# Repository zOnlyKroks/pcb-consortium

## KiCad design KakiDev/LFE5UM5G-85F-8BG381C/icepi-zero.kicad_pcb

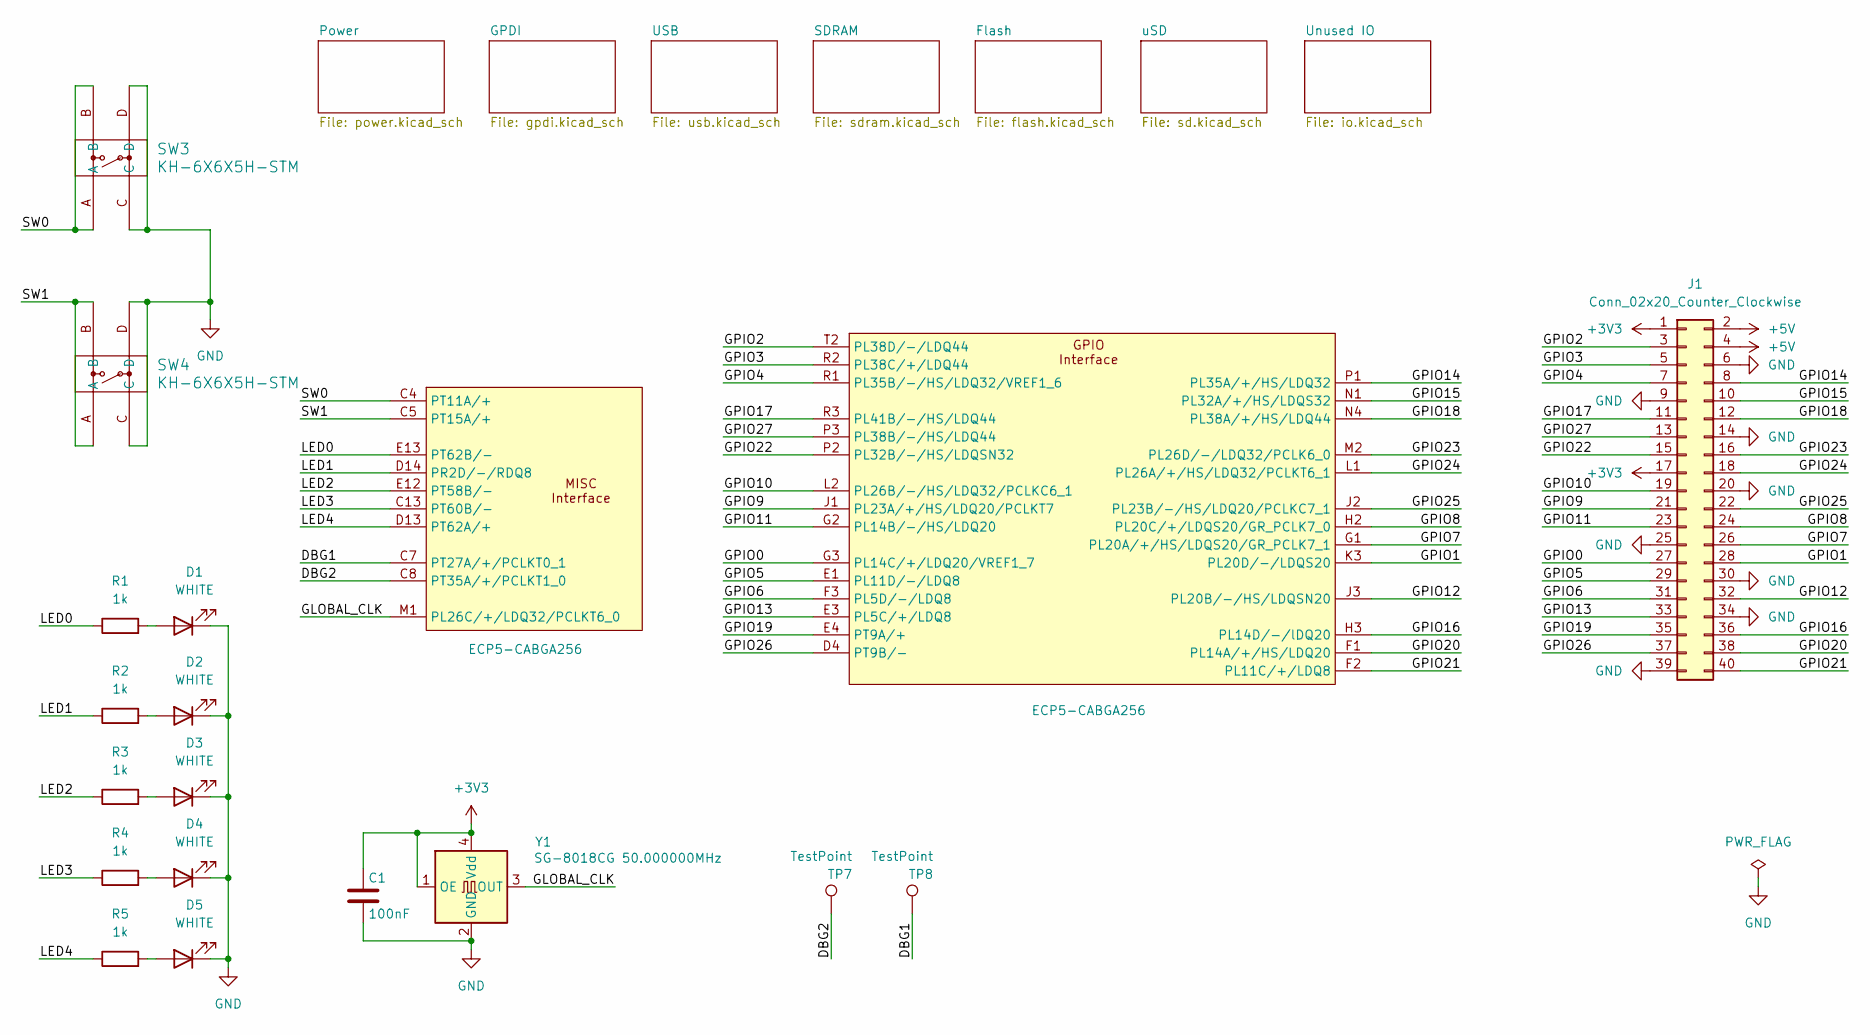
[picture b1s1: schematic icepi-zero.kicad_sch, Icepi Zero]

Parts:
C1: 100nF; C_0603_1608Metric; Manufactuer Part Number CL05B104KB54PNC; LCSC Part # C307331
D1, D2, D3, D4, D5: WHITE; LED_0603_1608Metric; Manufactuer Part Number KT-0603W; LCSC Part # C2290
J1: Conn_02x20_Counter_Clockwise; PinHeader_2x20_P2.54mm_Vertical
R1, R2, R3, R4, R5: 1k; R_0603_1608Metric; Manufactuer Part Number 0402WGF1001TCE; LCSC Part # C11702
SW3, SW4: KH-6X6X5H-STM; KH-6X6X5H-STM_SKE
TP7, TP8: TestPoint; TestPoint_Pad_D1.0mm
U1: ECP5-CABGA256; BGA-256_14.0x14.0mm_Layout16x16_P0.8mm_Ball0.45mm_Pad0.32mm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; Manufactuer Part Number LFE5U-25F-6BG256C; LCSC Part # C1521614
Y1: SG-8018CG 50.000000MHz; Oscillator_SMD_SiT_PQFN-4Pin_2.5x2.0mm; Manufactuer Part Number SG-8018CG 50.000000MHz TJHSA; LCSC Part # C390526

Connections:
+3V3: C1.1, J1.1, J1.17, Y1.1 (OE), Y1.4 (Vdd); also elsewhere on the board
+5V: J1.2, J1.4; also elsewhere on the board
/DBG1: TP8.1 (1_1), U1.C7 (PT27A/+/PCLKT0_1)
/DBG2: TP7.1 (1_1), U1.C8 (PT35A/+/PCLKT1_0)
/GLOBAL_CLK: U1.M1 (PL26C/+/LDQ32/PCLKT6_0), Y1.3 (OUT)
/GPIO0: J1.27, U1.G3 (PL14C/+/LDQ20/VREF1_7)
/GPIO1: J1.28, U1.K3 (PL20D/-/LDQS20)
/GPIO2: J1.3, U1.T2 (PL38D/-/LDQ44)
/GPIO3: J1.5, U1.R2 (PL38C/+/LDQ44)
/GPIO4: J1.7, U1.R1 (PL35B/-/HS/LDQ32/VREF1_6)
/GPIO5: J1.29, U1.E1 (PL11D/-/LDQ8)
/GPIO6: J1.31, U1.F3 (PL5D/-/LDQ8)
/GPIO7: J1.26, U1.G1 (PL20A/+/HS/LDQS20/GR_PCLK7_1)
/GPIO8: J1.24, U1.H2 (PL20C/+/LDQS20/GR_PCLK7_0)
/GPIO9: J1.21, U1.J1 (PL23A/+/HS/LDQ20/PCLKT7)
/GPIO10: J1.19, U1.L2 (PL26B/-/HS/LDQ32/PCLKC6_1)
/GPIO11: J1.23, U1.G2 (PL14B/-/HS/LDQ20)
/GPIO12: J1.32, U1.J3 (PL20B/-/HS/LDQSN20)
/GPIO13: J1.33, U1.E3 (PL5C/+/LDQ8)
/GPIO14: J1.8, U1.P1 (PL35A/+/HS/LDQ32)
/GPIO15: J1.10, U1.N1 (PL32A/+/HS/LDQS32)
/GPIO16: J1.36, U1.H3 (PL14D/-/lDQ20)
/GPIO17: J1.11, U1.R3 (PL41B/-/HS/LDQ44)
/GPIO18: J1.12, U1.N4 (PL38A/+/HS/LDQ44)
/GPIO19: J1.35, U1.E4 (PT9A/+)
/GPIO20: J1.38, U1.F1 (PL14A/+/HS/LDQ20)
/GPIO21: J1.40, U1.F2 (PL11C/+/LDQ8)
/GPIO22: J1.15, U1.P2 (PL32B/-/HS/LDQSN32)
/GPIO23: J1.16, U1.M2 (PL26D/-/LDQ32/PCLK6_0)
/GPIO24: J1.18, U1.L1 (PL26A/+/HS/LDQ32/PCLKT6_1)
/GPIO25: J1.22, U1.J2 (PL23B/-/HS/LDQ20/PCLKC7_1)
/GPIO26: J1.37, U1.D4 (PT9B/-)
/GPIO27: J1.13, U1.P3 (PL38B/-/HS/LDQ44)
/LED0: R1.1, U1.E13 (PT62B/-)
/LED1: R2.1, U1.D14 (PR2D/-/RDQ8)
/LED2: R3.1, U1.E12 (PT58B/-)
/LED3: R4.1, U1.C13 (PT60B/-)
/LED4: R5.1, U1.D13 (PT62A/+)
/SW0: SW3.A, SW3.B, U1.C4 (PT11A/+)
/SW1: SW4.A, SW4.B, U1.C5 (PT15A/+)
GND: C1.2, D1.1 (K), D2.1 (K), D3.1 (K), D4.1 (K), D5.1 (K), J1.6, J1.9, J1.14, J1.20, J1.25, J1.30, J1.34, J1.39, SW3.C, SW3.D, SW4.C, SW4.D, Y1.2 (GND); also elsewhere on the board
unnamed: D1.2 (A), R1.2
unnamed: D2.2 (A), R2.2
unnamed: D3.2 (A), R3.2
unnamed: D4.2 (A), R4.2
unnamed: D5.2 (A), R5.2

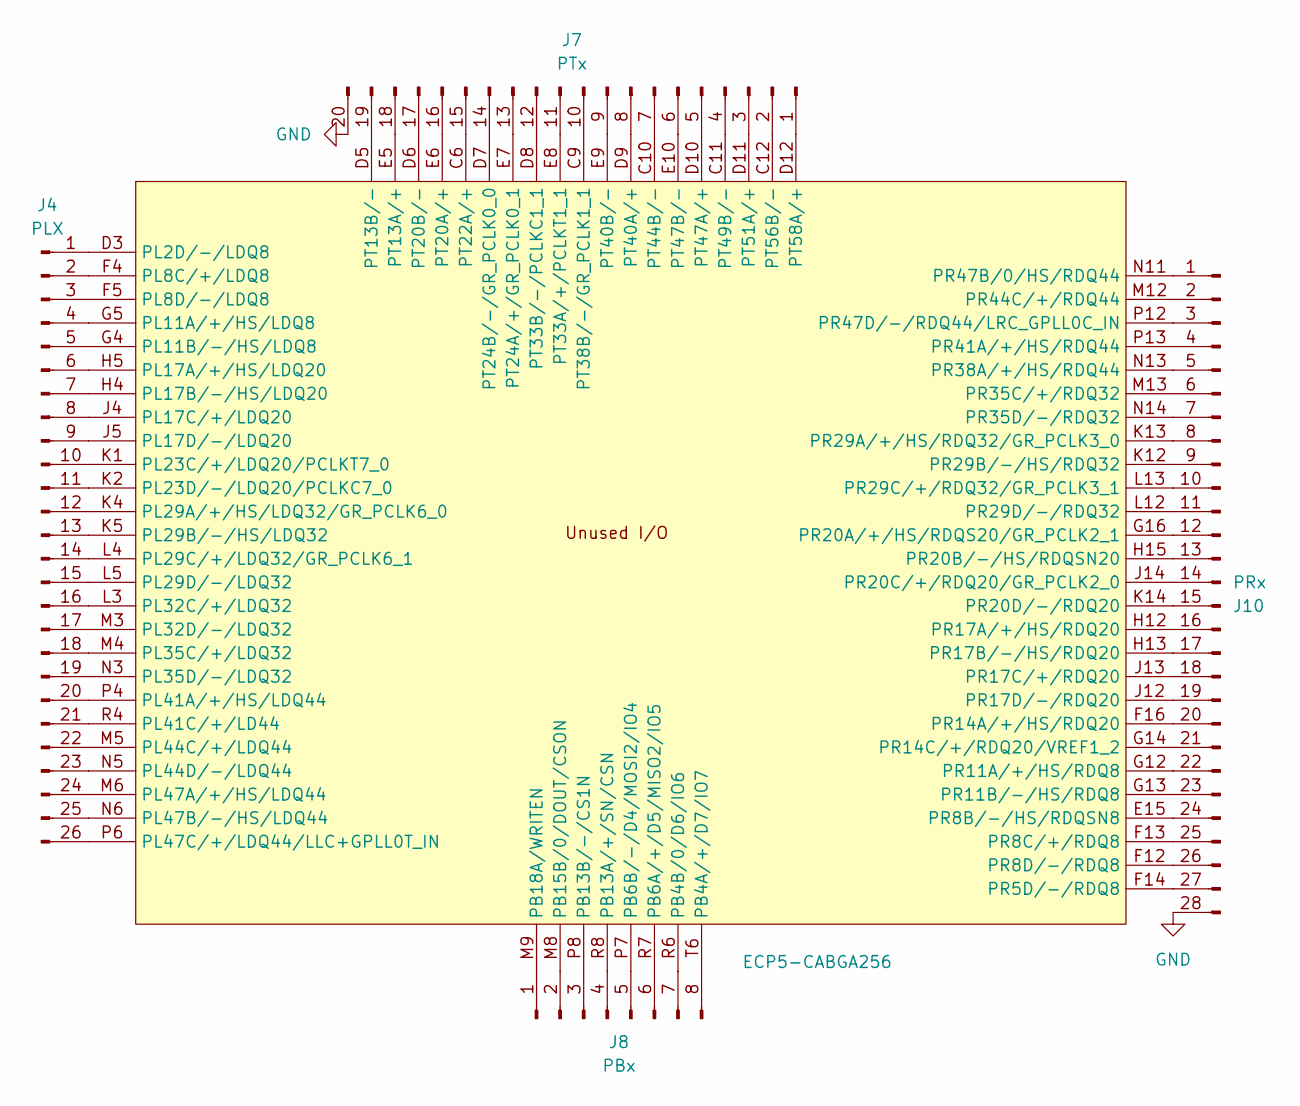
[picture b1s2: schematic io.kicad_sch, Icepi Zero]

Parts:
J4: PLX; PinHeader_2x13_P2.54mm_Vertical
J7: PTx; PinHeader_2x10_P2.54mm_Vertical
J8: PBx; PinHeader_2x04_P2.54mm_Vertical
J10: PRx; PinHeader_2x14_P2.54mm_Vertical
U1: ECP5-CABGA256; BGA-256_14.0x14.0mm_Layout16x16_P0.8mm_Ball0.45mm_Pad0.32mm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; Manufactuer Part Number LFE5U-25F-6BG256C; LCSC Part # C1521614

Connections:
GND: J7.20, J10.28; also elsewhere on the board
unnamed: J4.1, U1.D3 (PL2D/-/LDQ8)
unnamed: J4.2, U1.F4 (PL8C/+/LDQ8)
unnamed: J4.3, U1.F5 (PL8D/-/LDQ8)
unnamed: J4.4, U1.G5 (PL11A/+/HS/LDQ8)
unnamed: J4.5, U1.G4 (PL11B/-/HS/LDQ8)
unnamed: J4.6, U1.H5 (PL17A/+/HS/LDQ20)
unnamed: J4.7, U1.H4 (PL17B/-/HS/LDQ20)
unnamed: J4.8, U1.J4 (PL17C/+/LDQ20)
unnamed: J4.9, U1.J5 (PL17D/-/LDQ20)
unnamed: J4.10, U1.K1 (PL23C/+/LDQ20/PCLKT7_0)
unnamed: J4.11, U1.K2 (PL23D/-/LDQ20/PCLKC7_0)
unnamed: J4.12, U1.K4 (PL29A/+/HS/LDQ32/GR_PCLK6_0)
unnamed: J4.13, U1.K5 (PL29B/-/HS/LDQ32)
unnamed: J4.14, U1.L4 (PL29C/+/LDQ32/GR_PCLK6_1)
unnamed: J4.15, U1.L5 (PL29D/-/LDQ32)
unnamed: J4.16, U1.L3 (PL32C/+/LDQ32)
unnamed: J4.17, U1.M3 (PL32D/-/LDQ32)
unnamed: J4.18, U1.M4 (PL35C/+/LDQ32)
unnamed: J4.19, U1.N3 (PL35D/-/LDQ32)
unnamed: J4.20, U1.P4 (PL41A/+/HS/LDQ44)
unnamed: J4.21, U1.R4 (PL41C/+/LD44)
unnamed: J4.22, U1.M5 (PL44C/+/LDQ44)
unnamed: J4.23, U1.N5 (PL44D/-/LDQ44)
unnamed: J4.24, U1.M6 (PL47A/+/HS/LDQ44)
unnamed: J4.25, U1.N6 (PL47B/-/HS/LDQ44)
unnamed: J4.26, U1.P6 (PL47C/+/LDQ44/LLC+GPLL0T_IN)
unnamed: J7.1, U1.D12 (PT58A/+)
unnamed: J7.2, U1.C12 (PT56B/-)
unnamed: J7.3, U1.D11 (PT51A/+)
unnamed: J7.4, U1.C11 (PT49B/-)
unnamed: J7.5, U1.D10 (PT47A/+)
unnamed: J7.6, U1.E10 (PT47B/-)
unnamed: J7.7, U1.C10 (PT44B/-)
unnamed: J7.8, U1.D9 (PT40A/+)
unnamed: J7.9, U1.E9 (PT40B/-)
unnamed: J7.10, U1.C9 (PT38B/-/GR_PCLK1_1)
unnamed: J7.11, U1.E8 (PT33A/+/PCLKT1_1)
unnamed: J7.12, U1.D8 (PT33B/-/PCLKC1_1)
unnamed: J7.13, U1.E7 (PT24A/+/GR_PCLK0_1)
unnamed: J7.14, U1.D7 (PT24B/-/GR_PCLK0_0)
unnamed: J7.15, U1.C6 (PT22A/+)
unnamed: J7.16, U1.E6 (PT20A/+)
unnamed: J7.17, U1.D6 (PT20B/-)
unnamed: J7.18, U1.E5 (PT13A/+)
unnamed: J7.19, U1.D5 (PT13B/-)
unnamed: J8.1, U1.M9 (PB18A/WRITEN)
unnamed: J8.2, U1.M8 (PB15B/0/DOUT/CSON)
unnamed: J8.3, U1.P8 (PB13B/-/CS1N)
unnamed: J8.4, U1.R8 (PB13A/+/SN/CSN)
unnamed: J8.5, U1.P7 (PB6B/-/D4/MOSI2/IO4)
unnamed: J8.6, U1.R7 (PB6A/+/D5/MISO2/IO5)
unnamed: J8.7, U1.R6 (PB4B/0/D6/IO6)
unnamed: J8.8, U1.T6 (PB4A/+/D7/IO7)
unnamed: J10.1, U1.N11 (PR47B/0/HS/RDQ44)
unnamed: J10.2, U1.M12 (PR44C/+/RDQ44)
unnamed: J10.3, U1.P12 (PR47D/-/RDQ44/LRC_GPLL0C_IN)
unnamed: J10.4, U1.P13 (PR41A/+/HS/RDQ44)
unnamed: J10.5, U1.N13 (PR38A/+/HS/RDQ44)
unnamed: J10.6, U1.M13 (PR35C/+/RDQ32)
unnamed: J10.7, U1.N14 (PR35D/-/RDQ32)
unnamed: J10.8, U1.K13 (PR29A/+/HS/RDQ32/GR_PCLK3_0)
unnamed: J10.9, U1.K12 (PR29B/-/HS/RDQ32)
unnamed: J10.10, U1.L13 (PR29C/+/RDQ32/GR_PCLK3_1)
unnamed: J10.11, U1.L12 (PR29D/-/RDQ32)
unnamed: J10.12, U1.G16 (PR20A/+/HS/RDQS20/GR_PCLK2_1)
unnamed: J10.13, U1.H15 (PR20B/-/HS/RDQSN20)
unnamed: J10.14, U1.J14 (PR20C/+/RDQ20/GR_PCLK2_0)
unnamed: J10.15, U1.K14 (PR20D/-/RDQ20)
unnamed: J10.16, U1.H12 (PR17A/+/HS/RDQ20)
unnamed: J10.17, U1.H13 (PR17B/-/HS/RDQ20)
unnamed: J10.18, U1.J13 (PR17C/+/RDQ20)
unnamed: J10.19, U1.J12 (PR17D/-/RDQ20)
unnamed: J10.20, U1.F16 (PR14A/+/HS/RDQ20)
unnamed: J10.21, U1.G14 (PR14C/+/RDQ20/VREF1_2)
unnamed: J10.22, U1.G12 (PR11A/+/HS/RDQ8)
unnamed: J10.23, U1.G13 (PR11B/-/HS/RDQ8)
unnamed: J10.24, U1.E15 (PR8B/-/HS/RDQSN8)
unnamed: J10.25, U1.F13 (PR8C/+/RDQ8)
unnamed: J10.26, U1.F12 (PR8D/-/RDQ8)
unnamed: J10.27, U1.F14 (PR5D/-/RDQ8)

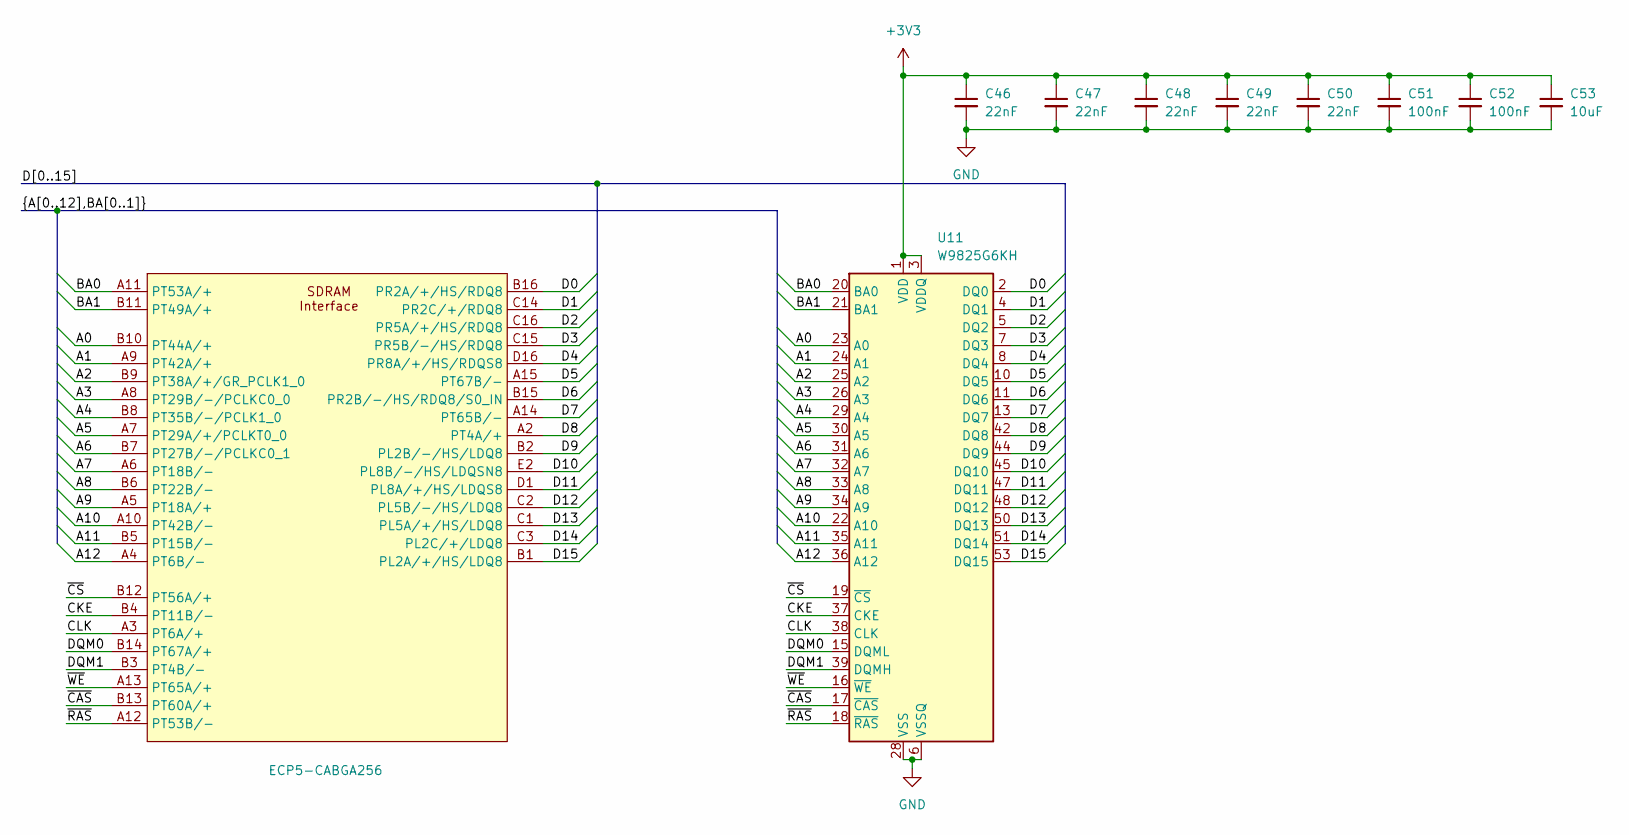
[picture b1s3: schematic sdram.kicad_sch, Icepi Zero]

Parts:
C46, C47, C48, C49, C50: 22nF; C_0603_1608Metric; Manufactuer Part Number 0603B223K500NT; LCSC Part # C77571
C51, C52: 100nF; C_0603_1608Metric; Manufactuer Part Number 0603B223K500NT; LCSC Part # C77571
C53: 10uF; C_0603_1608Metric; Manufactuer Part Number CL10A106KP8NNNC; LCSC Part # C19702
U1: ECP5-CABGA256; BGA-256_14.0x14.0mm_Layout16x16_P0.8mm_Ball0.45mm_Pad0.32mm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; Manufactuer Part Number LFE5U-25F-6BG256C; LCSC Part # C1521614
U11: W9825G6KH; TSOP-II-54_22.2x10.16mm_P0.8mm; Manufactuer Part Number W9825G6KH-6; LCSC Part # C62246

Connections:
+3V3: C46.1, C47.1, C48.1, C49.1, C50.1, C51.1, C52.1, C53.1, U11.1 (VDD), U11.3 (VDDQ), U11.9 (VDDQ), U11.14 (VDD), U11.27 (VDD), U11.43 (VDDQ), U11.49 (VDDQ); also elsewhere on the board
/SDRAM/A0: U1.B10 (PT44A/+), U11.23 (A0)
/SDRAM/A1: U1.A9 (PT42A/+), U11.24 (A1)
/SDRAM/A2: U1.B9 (PT38A/+/GR_PCLK1_0), U11.25 (A2)
/SDRAM/A3: U1.A8 (PT29B/-/PCLKC0_0), U11.26 (A3)
/SDRAM/A4: U1.B8 (PT35B/-/PCLK1_0), U11.29 (A4)
/SDRAM/A5: U1.A7 (PT29A/+/PCLKT0_0), U11.30 (A5)
/SDRAM/A6: U1.B7 (PT27B/-/PCLKC0_1), U11.31 (A6)
/SDRAM/A7: U1.A6 (PT18B/-), U11.32 (A7)
/SDRAM/A8: U1.B6 (PT22B/-), U11.33 (A8)
/SDRAM/A9: U1.A5 (PT18A/+), U11.34 (A9)
/SDRAM/A10: U1.A10 (PT42B/-), U11.22 (A10)
/SDRAM/A11: U1.B5 (PT15B/-), U11.35 (A11)
/SDRAM/A12: U1.A4 (PT6B/-), U11.36 (A12)
/SDRAM/BA0: U1.A11 (PT53A/+), U11.20 (BA0)
/SDRAM/BA1: U1.B11 (PT49A/+), U11.21 (BA1)
/SDRAM/CKE: U1.B4 (PT11B/-), U11.37 (CKE)
/SDRAM/CLK: U1.A3 (PT6A/+), U11.38 (CLK)
/SDRAM/D0: U1.B16 (PR2A/+/HS/RDQ8), U11.2 (DQ0)
/SDRAM/D1: U1.C14 (PR2C/+/RDQ8), U11.4 (DQ1)
/SDRAM/D2: U1.C16 (PR5A/+/HS/RDQ8), U11.5 (DQ2)
/SDRAM/D3: U1.C15 (PR5B/-/HS/RDQ8), U11.7 (DQ3)
/SDRAM/D4: U1.D16 (PR8A/+/HS/RDQS8), U11.8 (DQ4)
/SDRAM/D5: U1.A15 (PT67B/-), U11.10 (DQ5)
/SDRAM/D6: U1.B15 (PR2B/-/HS/RDQ8/S0_IN), U11.11 (DQ6)
/SDRAM/D7: U1.A14 (PT65B/-), U11.13 (DQ7)
/SDRAM/D8: U1.A2 (PT4A/+), U11.42 (DQ8)
/SDRAM/D9: U1.B2 (PL2B/-/HS/LDQ8), U11.44 (DQ9)
/SDRAM/D10: U1.E2 (PL8B/-/HS/LDQSN8), U11.45 (DQ10)
/SDRAM/D11: U1.D1 (PL8A/+/HS/LDQS8), U11.47 (DQ11)
/SDRAM/D12: U1.C2 (PL5B/-/HS/LDQ8), U11.48 (DQ12)
/SDRAM/D13: U1.C1 (PL5A/+/HS/LDQ8), U11.50 (DQ13)
/SDRAM/D14: U1.C3 (PL2C/+/LDQ8), U11.51 (DQ14)
/SDRAM/D15: U1.B1 (PL2A/+/HS/LDQ8), U11.53 (DQ15)
/SDRAM/DQM0: U1.B14 (PT67A/+), U11.15 (DQML)
/SDRAM/DQM1: U1.B3 (PT4B/-), U11.39 (DQMH)
/SDRAM/~CAS: U1.B13 (PT60A/+), U11.17 (~CAS)
/SDRAM/~CS: U1.B12 (PT56A/+), U11.19 (~CS)
/SDRAM/~RAS: U1.A12 (PT53B/-), U11.18 (~RAS)
/SDRAM/~WE: U1.A13 (PT65A/+), U11.16 (~WE)
GND: C46.2, C47.2, C48.2, C49.2, C50.2, C51.2, C52.2, C53.2, U11.6 (VSSQ), U11.12 (VSSQ), U11.28 (VSS), U11.41 (VSS), U11.46 (VSSQ), U11.52 (VSSQ), U11.54 (VSS); also elsewhere on the board

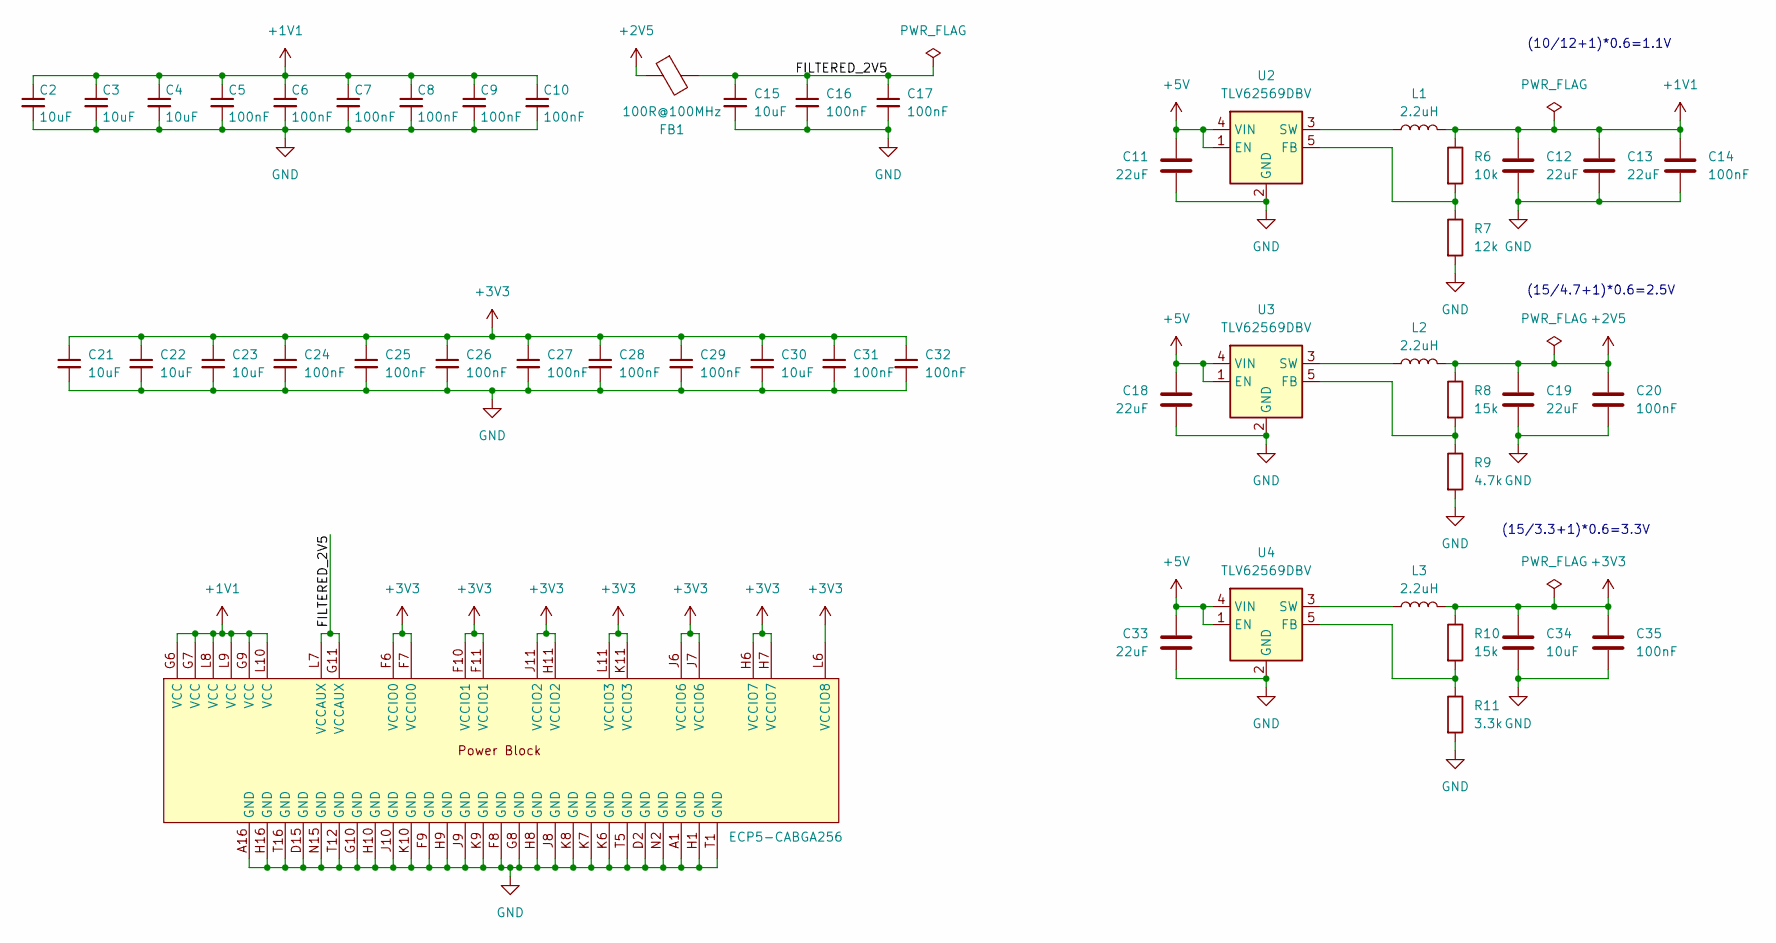
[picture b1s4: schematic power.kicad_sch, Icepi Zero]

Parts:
C2, C3, C4, C15, C21, C22, C23, C30, C34: 10uF; C_0603_1608Metric; Manufactuer Part Number CL10A106KP8NNNC; LCSC Part # C19702
C5, C6, C7, C8, C9, C10, C14, C16, C17, C20, C24, C25, C26, C27, C28, C29, C31, C32, C35: 100nF; C_0603_1608Metric; Manufactuer Part Number CL05B104KB54PNC; LCSC Part # C307331
C11, C12, C13, C18, C19, C33: 22uF; C_0603_1608Metric; Manufactuer Part Number CL10A226MQ8NRNC; LCSC Part # C59461
FB1: 100R@100MHz; L_0805_2012Metric; Manufactuer Part Number CBG201209U101T; LCSC Part # C74480
L1, L2, L3: 2.2uH; L_0805_2012Metric; Manufactuer Part Number TDK MLP2012S2R2MT0S1; LCSC Part # C107322
R6: 10k; R_0603_1608Metric; Manufactuer Part Number 0402WGF1002TCE; LCSC Part # C25744
R7: 12k; R_0603_1608Metric; Manufactuer Part Number 0402WGF1202TCE; LCSC Part # C25752
R8, R10: 15k; R_0603_1608Metric; Manufactuer Part Number 0402WGF1502TCE; LCSC Part # C25756
R9: 4.7k; R_0603_1608Metric; Manufactuer Part Number 0402WGF4701TCE; LCSC Part # C25900
R11: 3.3k; R_0603_1608Metric; Manufactuer Part Number 0402WGF3301TCE; LCSC Part # C25890
U1: ECP5-CABGA256; BGA-256_14.0x14.0mm_Layout16x16_P0.8mm_Ball0.45mm_Pad0.32mm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; Manufactuer Part Number LFE5U-25F-6BG256C; LCSC Part # C1521614
U2, U3, U4: TLV62569DBV; SOT-23-5; Manufactuer Part Number TLV62569DBVR; LCSC Part # C141836

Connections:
+1V1: C2.1, C3.1, C4.1, C5.1, C6.1, C7.1, C8.1, C9.1, C10.1, C12.1, C13.1, C14.1, L1.2, R6.1, U1.G6 (VCC), U1.G7 (VCC), U1.G9 (VCC), U1.L8 (VCC), U1.L9 (VCC), U1.L10 (VCC)
+2V5: C19.1, C20.1, FB1.1, L2.2, R8.1
+3V3: C21.1, C22.1, C23.1, C24.1, C25.1, C26.1, C27.1, C28.1, C29.1, C30.1, C31.1, C32.1, C34.1, C35.1, L3.2, R10.1, U1.F6 (VCCIO0), U1.F7 (VCCIO0), U1.F10 (VCCIO1), U1.F11 (VCCIO1), U1.H6 (VCCIO7), U1.H7 (VCCIO7), U1.H11 (VCCIO2), U1.J6 (VCCIO6), U1.J7 (VCCIO6), U1.J11 (VCCIO2), U1.K11 (VCCIO3), U1.L6 (VCCIO8), U1.L11 (VCCIO3); also elsewhere on the board
+5V: C11.1, C18.1, C33.1, U2.1 (EN), U2.4 (VIN), U3.1 (EN), U3.4 (VIN), U4.1 (EN), U4.4 (VIN); also elsewhere on the board
/Power/FILTERED_2V5: C15.1, C16.1, C17.1, FB1.2, U1.G11 (VCCAUX), U1.L7 (VCCAUX)
GND: C2.2, C3.2, C4.2, C5.2, C6.2, C7.2, C8.2, C9.2, C10.2, C11.2, C12.2, C13.2, C14.2, C15.2, C16.2, C17.2, C18.2, C19.2, C20.2, C21.2, C22.2, C23.2, C24.2, C25.2, C26.2, C27.2, C28.2, C29.2, C30.2, C31.2, C32.2, C33.2, C34.2, C35.2, R7.2, R9.2, R11.2, U1.A1 (GND), U1.A16 (GND), U1.D2 (GND), U1.D15 (GND), U1.F8 (GND), U1.F9 (GND), U1.G8 (GND), U1.G10 (GND), U1.H1 (GND), U1.H8 (GND), U1.H9 (GND), U1.H10 (GND), U1.H16 (GND), U1.J8 (GND), U1.J9 (GND), U1.J10 (GND), U1.K6 (GND), U1.K7 (GND), U1.K8 (GND), U1.K9 (GND), U1.K10 (GND), U1.N2 (GND), U1.N15 (GND), U1.T1 (GND), U1.T5 (GND), U1.T12 (GND), U1.T16 (GND), U2.2 (GND), U3.2 (GND), U4.2 (GND); also elsewhere on the board
unnamed: R6.2, R7.1, U2.5 (FB)
unnamed: L1.1, U2.3 (SW)
unnamed: R8.2, R9.1, U3.5 (FB)
unnamed: L2.1, U3.3 (SW)
unnamed: R10.2, R11.1, U4.5 (FB)
unnamed: L3.1, U4.3 (SW)

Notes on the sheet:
(15/4.7+1)*0.6=2.5V
(10/12+1)*0.6=1.1V
(15/3.3+1)*0.6=3.3V

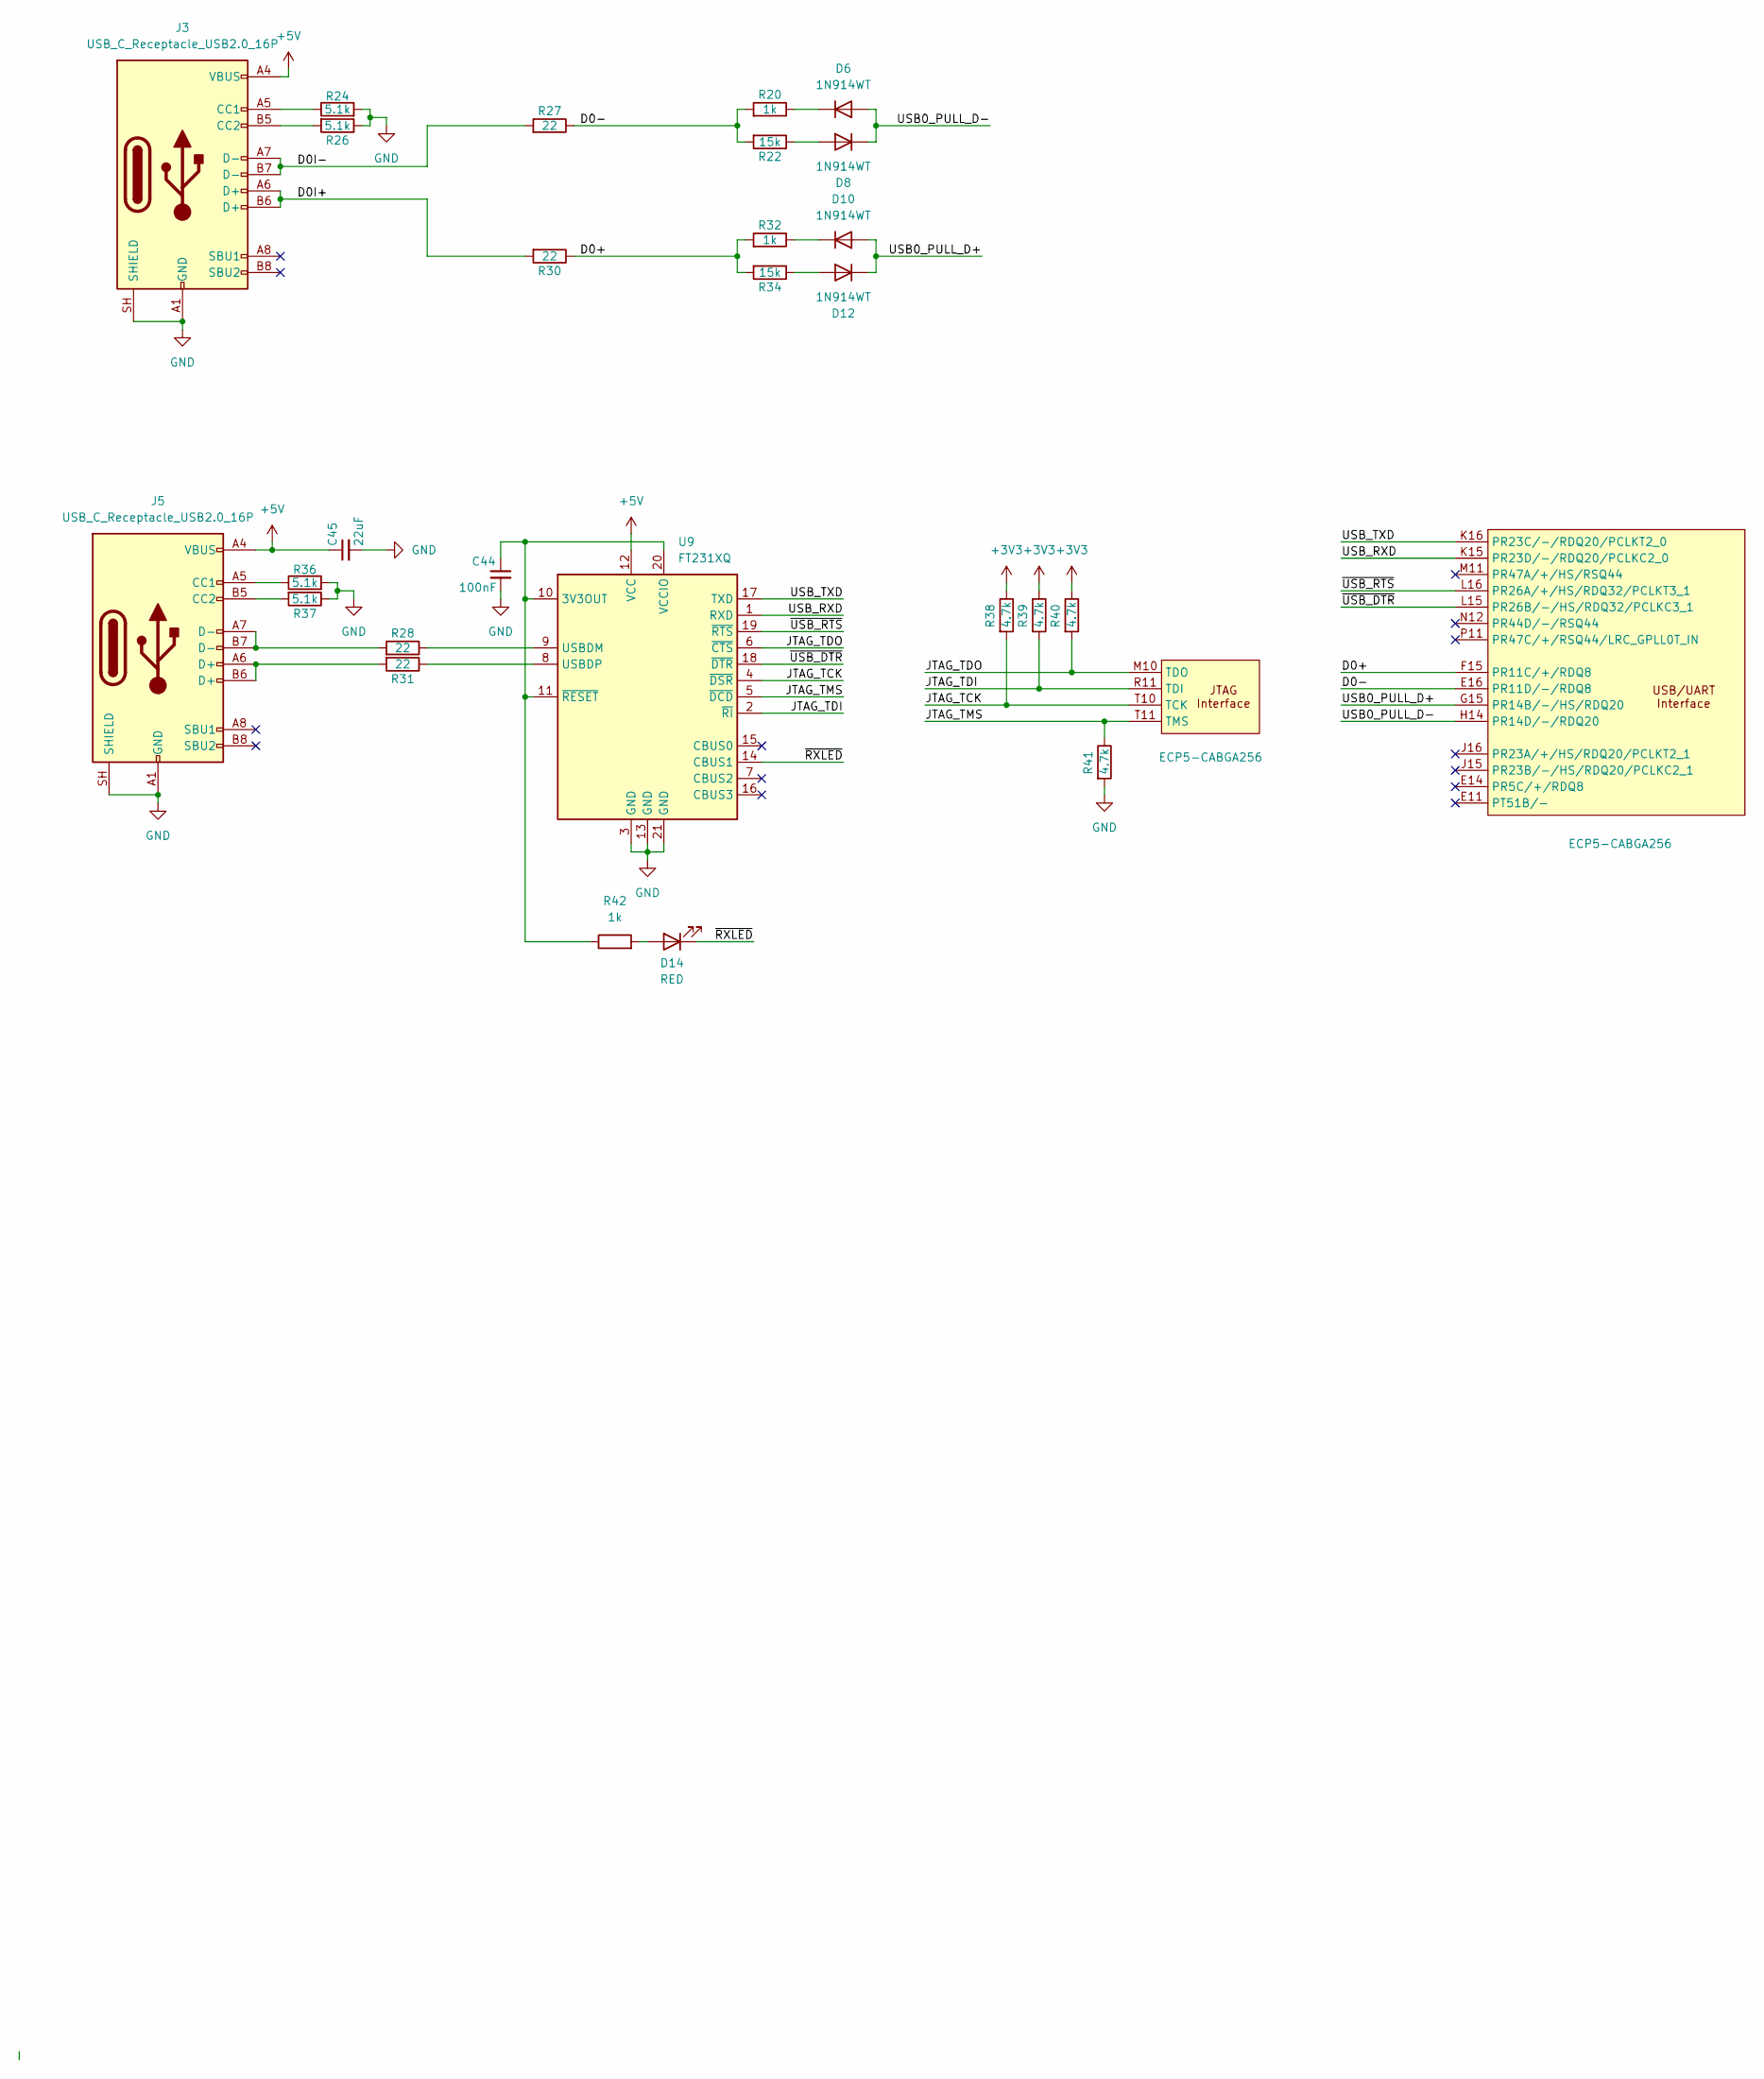
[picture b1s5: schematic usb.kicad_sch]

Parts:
C44: 100nF; C_0603_1608Metric; Manufactuer Part Number CL05B104KB54PNC; LCSC Part # C307331
C45: 22uF; C_0603_1608Metric; Manufactuer Part Number CL10A226MQ8NRNC; LCSC Part # C59461
D6, D8, D10, D12: 1N914WT; D_SOD-523; Manufactuer Part Number 1N914WT; LCSC Part # C2836064
D14: RED; LED_0603_1608Metric; Manufactuer Part Number KT-0603R; LCSC Part # C2286
J3, J5: USB_C_Receptacle_USB2.0_16P; USB_C_Receptacle_HRO_TYPE-C-31-M-12
R20, R32, R42: 1k; R_0603_1608Metric; Manufactuer Part Number 0402WGF1001TCE; LCSC Part # C11702
R22: 15k; R_0603_1608Metric; Manufactuer Part Number 0402WGF1502TCE; LCSC Part # C25756
R24, R26, R36, R37: 5.1k; R_0603_1608Metric; Manufactuer Part Number 0402WGF5101TCE; LCSC Part # C25905
R27, R28, R30, R31: 22; R_0603_1608Metric; Manufactuer Part Number 0201WMF270JTEE; LCSC Part # C473051
R34: 15k; R_0402_1005Metric; Manufactuer Part Number 0402WGF1502TCE; LCSC Part # C25756
R38, R39, R40, R41: 4.7k; R_0603_1608Metric; Manufactuer Part Number 0402WGF4701TCE; LCSC Part # C25900
U1: ECP5-CABGA256; BGA-256_14.0x14.0mm_Layout16x16_P0.8mm_Ball0.45mm_Pad0.32mm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; Manufactuer Part Number LFE5U-25F-6BG256C; LCSC Part # C1521614
U9: FT231XQ; QFN-20-1EP_4x4mm_P0.5mm_EP2.5x2.5mm; Manufactuer Part Number FT231XQ-R; LCSC Part # C132159

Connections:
+3V3: R38.1, R39.1, R40.1; also elsewhere on the board
+5V: C45.1, J3.A4 (VBUS), J3.A9 (VBUS), J3.B4 (VBUS), J3.B9 (VBUS), J5.A4 (VBUS), J5.A9 (VBUS), J5.B4 (VBUS), J5.B9 (VBUS), U9.12 (VCC); also elsewhere on the board
/USB/D0+: R30.1, R32.2, R34.2, U1.F15 (PR11C/+/RDQ8)
/USB/D0-: R20.2, R22.2, R27.1, U1.E16 (PR11D/-/RDQ8)
/USB/D0I+: J3.A6 (D+), J3.B6 (D+), R30.2
/USB/D0I-: J3.A7 (D-), J3.B7 (D-), R27.2
/USB/JTAG_TCK: R38.2, U1.T10 (TCK), U9.4 (~DSR)
/USB/JTAG_TDI: R39.2, U1.R11 (TDI), U9.2 (~RI)
/USB/JTAG_TDO: R40.2, U1.M10 (TDO), U9.6 (~CTS)
/USB/JTAG_TMS: R41.1, U1.T11 (TMS), U9.5 (~DCD)
/USB/USB0_PULL_D+: D10.2 (A), D12.1 (K), U1.G15 (PR14B/-/HS/RDQ20)
/USB/USB0_PULL_D-: D6.2 (A), D8.1 (K), U1.H14 (PR14D/-/RDQ20)
/USB/USB_RXD: U1.K15 (PR23D/-/RDQ20/PCLKC2_0), U9.1 (RXD)
/USB/USB_TXD: U1.K16 (PR23C/-/RDQ20/PCLKT2_0), U9.17 (TXD)
/USB/~RXLED: D14.1 (K), U9.14 (CBUS1)
/USB/~USB_DTR: U1.L15 (PR26B/-/HS/RDQ32/PCLKC3_1), U9.18 (~DTR)
/USB/~USB_RTS: U1.L16 (PR26A/+/HS/RDQ32/PCLKT3_1), U9.19 (~RTS)
GND: C44.2, C45.2, J3.A1 (GND), J3.A12 (GND), J3.B1 (GND), J3.B12 (GND), J3.SH (SHIELD), J5.A1 (GND), J5.A12 (GND), J5.B1 (GND), J5.B12 (GND), J5.SH (SHIELD), R24.2, R26.1, R36.2, R37.1, R41.2, U9.3 (GND), U9.13 (GND), U9.21 (GND); also elsewhere on the board
unnamed: D6.1 (K), R20.1
unnamed: D8.2 (A), R22.1
unnamed: D10.1 (K), R32.1
unnamed: D12.2 (A), R34.1
unnamed: D14.2 (A), R42.2
unnamed: J3.A5 (CC1), R24.1
unnamed: J3.B5 (CC2), R26.2
unnamed: J5.A5 (CC1), R36.1
unnamed: J5.B5 (CC2), R37.2
unnamed: J5.A6 (D+), J5.B6 (D+), R31.2
unnamed: J5.A7 (D-), J5.B7 (D-), R28.2
unnamed: C44.1, R42.1, U9.10 (3V3OUT), U9.11 (~RESET), U9.20 (VCCIO)
unnamed: R28.1, U9.9 (USBDM)
unnamed: R31.1, U9.8 (USBDP)

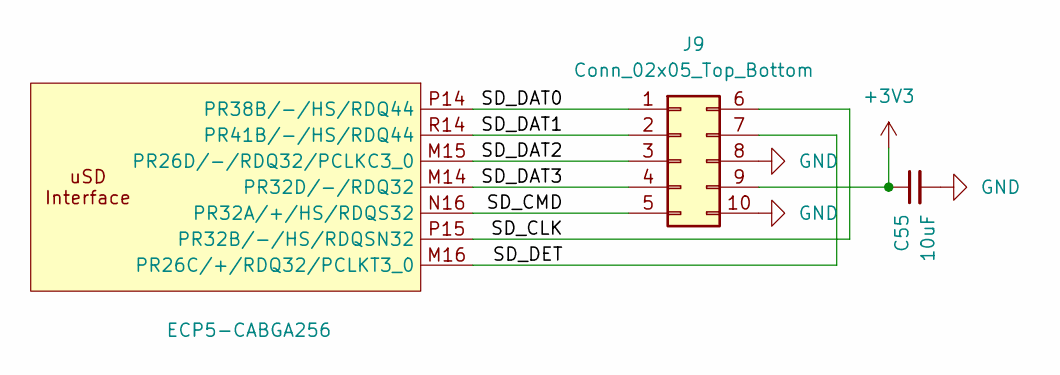
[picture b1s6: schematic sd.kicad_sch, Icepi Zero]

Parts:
C55: 10uF; C_0603_1608Metric; Manufactuer Part Number CL10A106KP8NNNC; LCSC Part # C19702
J9: Conn_02x05_Top_Bottom; PinHeader_2x05_P2.54mm_Vertical
U1: ECP5-CABGA256; BGA-256_14.0x14.0mm_Layout16x16_P0.8mm_Ball0.45mm_Pad0.32mm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; Manufactuer Part Number LFE5U-25F-6BG256C; LCSC Part # C1521614

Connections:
+3V3: C55.1, J9.9; also elsewhere on the board
/uSD/SD_CLK: J9.6, U1.P15 (PR32B/-/HS/RDQSN32)
/uSD/SD_CMD: J9.5, U1.N16 (PR32A/+/HS/RDQS32)
/uSD/SD_DAT0: J9.1, U1.P14 (PR38B/-/HS/RDQ44)
/uSD/SD_DAT1: J9.2, U1.R14 (PR41B/-/HS/RDQ44)
/uSD/SD_DAT2: J9.3, U1.M15 (PR26D/-/RDQ32/PCLKC3_0)
/uSD/SD_DAT3: J9.4, U1.M14 (PR32D/-/RDQ32)
/uSD/SD_DET: J9.7, U1.M16 (PR26C/+/RDQ32/PCLKT3_0)
GND: C55.2, J9.8, J9.10; also elsewhere on the board

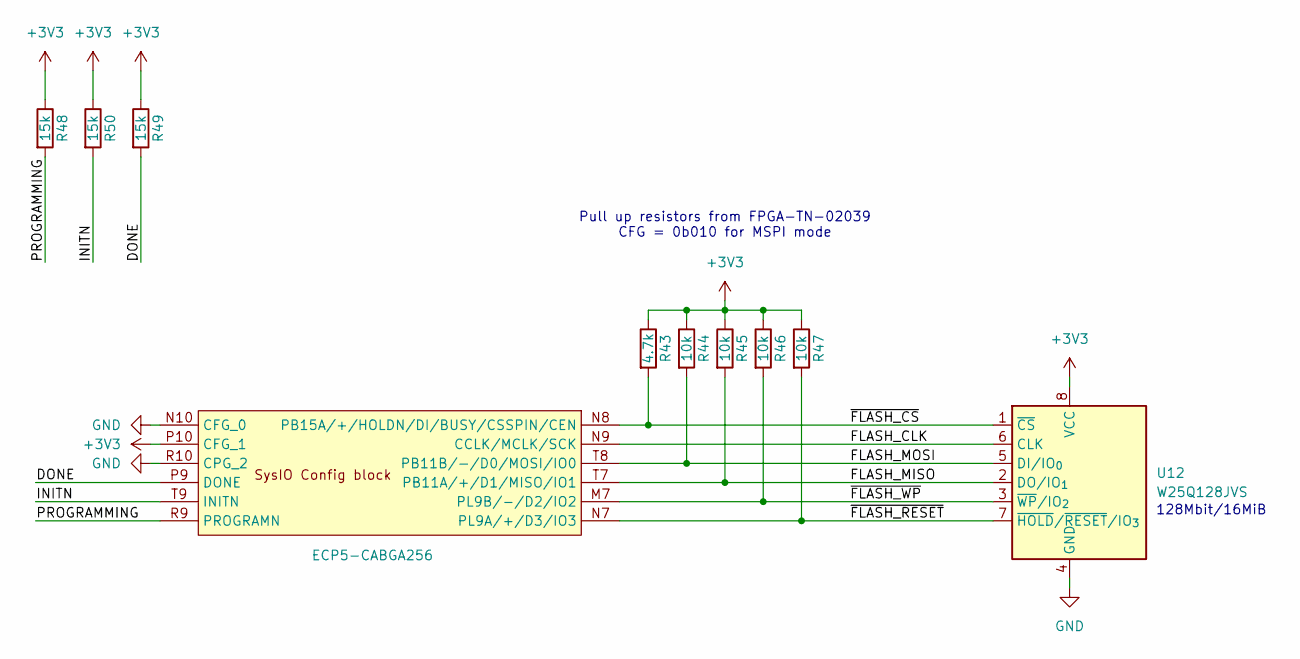
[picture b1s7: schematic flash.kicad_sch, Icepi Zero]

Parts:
R43: 4.7k; R_0603_1608Metric; Manufactuer Part Number 0402WGF4701TCE; LCSC Part # C25900
R44, R45, R46, R47: 10k; R_0603_1608Metric; Manufactuer Part Number 0402WGF1002TCE; LCSC Part # C25744
R48, R49, R50: 15k; R_0603_1608Metric; Manufactuer Part Number 0402WGF1502TCE; LCSC Part # C25756
U1: ECP5-CABGA256; BGA-256_14.0x14.0mm_Layout16x16_P0.8mm_Ball0.45mm_Pad0.32mm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; Manufactuer Part Number LFE5U-25F-6BG256C; LCSC Part # C1521614
U12: W25Q128JVS; SOIC-8_5.3x5.3mm_P1.27mm; Manufactuer Part Number W25Q128JVSIQ; LCSC Part # C97521

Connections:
+3V3: R43.1, R44.1, R45.1, R46.1, R47.1, R48.1, R49.1, R50.1, U1.P10 (CFG_1), U12.8 (VCC); also elsewhere on the board
/Flash/DONE: R49.2, U1.P9 (DONE)
/Flash/FLASH_CLK: U1.N9 (CCLK/MCLK/SCK), U12.6 (CLK)
/Flash/FLASH_MISO: R45.2, U1.T7 (PB11A/+/D1/MISO/IO1), U12.2 (DO/IO_{1})
/Flash/FLASH_MOSI: R44.2, U1.T8 (PB11B/-/D0/MOSI/IO0), U12.5 (DI/IO_{0})
/Flash/INITN: R50.2, U1.T9 (INITN)
/Flash/PROGRAMMING: R48.2, U1.R9 (PROGRAMN)
/Flash/~FLASH_CS: R43.2, U1.N8 (PB15A/+/HOLDN/DI/BUSY/CSSPIN/CEN), U12.1 (~CS)
/Flash/~FLASH_RESET: R47.2, U1.N7 (PL9A/+/D3/IO3), U12.7 (~HOLD/~RESET/IO_{3})
/Flash/~FLASH_WP: R46.2, U1.M7 (PL9B/-/D2/IO2), U12.3 (~WP/IO_{2})
GND: U1.N10 (CFG_0), U1.R10 (CPG_2), U12.4 (GND); also elsewhere on the board

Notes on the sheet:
128Mbit/16MiB
Pull up resistors from FPGA-TN-02039 CFG = 0b010 for MSPI mode

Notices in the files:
KakiDev/LFE5UM5G-85F-8BG381C/flash.kicad_sch:
License: Solderpad
